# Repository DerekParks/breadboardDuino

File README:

A simple arduino clone for plugging into breadboards or protoboard.

For me by me. I know nothing about electronics. This probably doesn't work.

#References
http://www.fiz-ix.com/2012/11/schematic-of-a-breadboard-arduino/
http://jobs.arduinoexperts.com/wp-content/uploads/2013/03/atmega328w.png

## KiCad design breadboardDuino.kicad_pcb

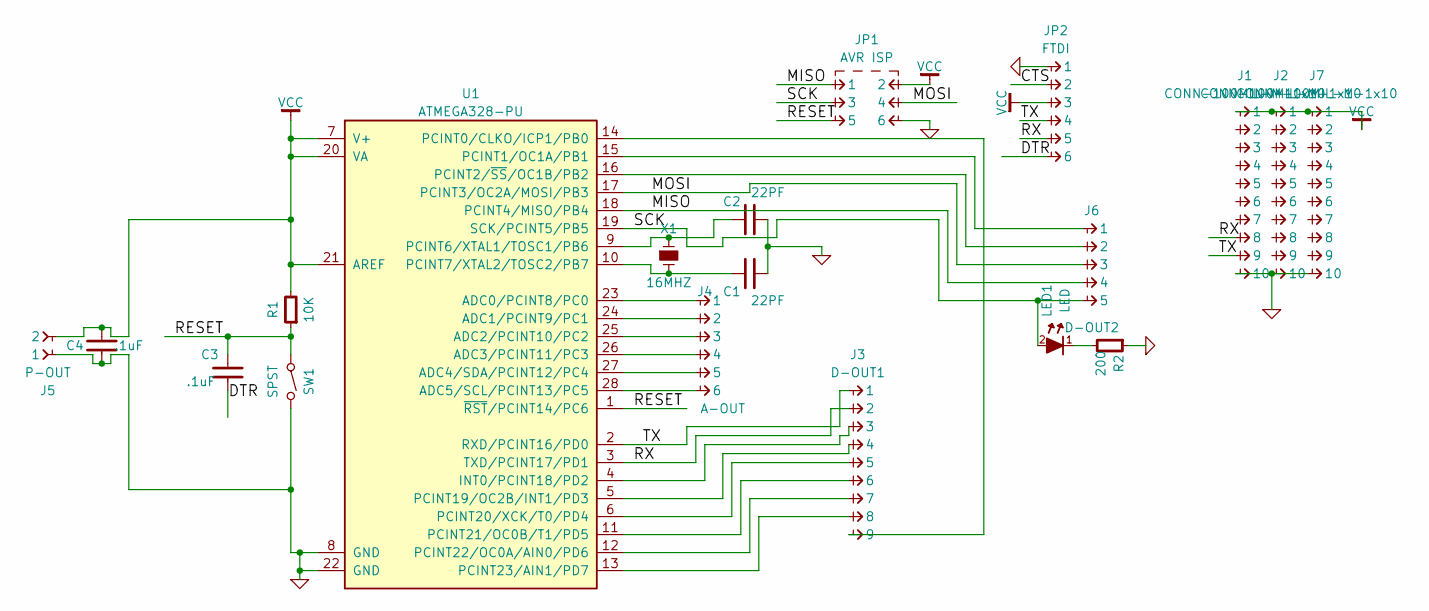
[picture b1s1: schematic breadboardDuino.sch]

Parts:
C1, C2: 22PF; C-CER-3mm
C3, C4: .1uF; C-CER-3mm
J1, J2, J7: CONN-100MIL-M-1x10
J3: D-OUT1; CONN-100MIL-M-1x9
J4: A-OUT; CONN-100MIL-M-1x6
J5: P-OUT; CONN-100MIL-F-1x2
J6: D-OUT2; CONN-100MIL-M-1x5
JP1: AVR ISP; CONN-100MIL-M-2x3
JP2: FTDI; CONN-100MIL-M-1x6
LED1: LED; LED-5mm
R1: 10K; R-125mW
R2: 200; R-125mW
SW1: SPST; B3F-10XX
U1: ATMEGA328-PU; DIP-28; MPN ATMEGA328-PU
X1: 16MHZ; XTAL-HC49US

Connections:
/CTS: JP2.2
/DTR: C3.2, JP2.6
/MISO: J6.4, JP1.1, U1.18 (PCINT4/MISO/PB4)
/MOSI: J6.3, JP1.4, U1.17 (PCINT3/OC2A/MOSI/PB3)
/RESET: C3.1, JP1.5, R1.1, SW1.1, U1.1 (~RST~/PCINT14/PC6)
/RX: J1.8, J3.2, JP2.5, U1.3 (TXD/PCINT17/PD1)
/SCK: J6.5, JP1.3, LED1.2 (A), U1.19 (SCK/PCINT5/PB5)
/TX: J1.9, J3.1, JP2.4, U1.2 (RXD/PCINT16/PD0)
GND: C1.1, C2.1, C4.2, J1.10, J2.10, J5.1, J7.10, JP1.6, JP2.1, R2.1, SW1.2, U1.8 (GND), U1.22 (GND)
unnamed: C1.2, U1.10 (PCINT7/XTAL2/TOSC2/PB7), X1.2
unnamed: C2.2, U1.9 (PCINT6/XTAL1/TOSC1/PB6), X1.1
unnamed: J3.3, U1.4 (INT0/PCINT18/PD2)
unnamed: J3.4, U1.5 (PCINT19/OC2B/INT1/PD3)
unnamed: J3.5, U1.6 (PCINT20/XCK/T0/PD4)
unnamed: J3.6, U1.11 (PCINT21/OC0B/T1/PD5)
unnamed: J3.7, U1.12 (PCINT22/OC0A/AIN0/PD6)
unnamed: J3.8, U1.13 (PCINT23/AIN1/PD7)
unnamed: J3.9, U1.14 (PCINT0/CLKO/ICP1/PB0)
unnamed: J4.1, U1.23 (ADC0/PCINT8/PC0)
unnamed: J4.2, U1.24 (ADC1/PCINT9/PC1)
unnamed: J4.3, U1.25 (ADC2/PCINT10/PC2)
unnamed: J4.4, U1.26 (ADC3/PCINT11/PC3)
unnamed: J4.5, U1.27 (ADC4/SDA/PCINT12/PC4)
unnamed: J4.6, U1.28 (ADC5/SCL/PCINT13/PC5)
unnamed: J6.1, U1.15 (PCINT1/OC1A/PB1)
unnamed: J6.2, U1.16 (PCINT2/~SS~/OC1B/PB2)
unnamed: LED1.1 (K), R2.2
VCC: C4.1, J1.1, J2.1, J5.2, J7.1, JP1.2, JP2.3, R1.2, U1.7 (V+), U1.20 (VA), U1.21 (AREF)

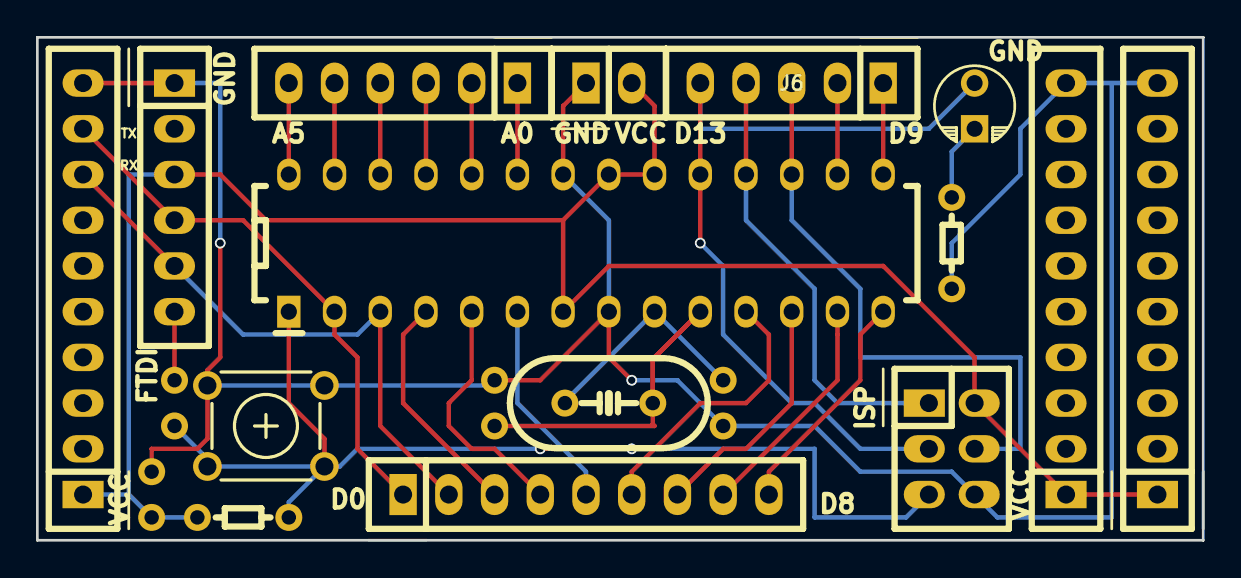
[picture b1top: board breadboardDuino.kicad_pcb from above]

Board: 2 copper layers, 64.8 x 27.9 mm, 19 parts (0 on the bottom side), 27 nets.

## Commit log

2017-04-19 inital commit
2017-04-21 Readme
2017-04-21 Inital layout
2017-04-21 Added some proto on the eges
2017-04-24 Finished layout
